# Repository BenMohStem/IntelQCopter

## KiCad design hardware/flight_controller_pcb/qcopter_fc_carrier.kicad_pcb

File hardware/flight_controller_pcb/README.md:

# Flight-controller carrier PCB — draft 0

This first editable PCB is a **logic/sensor carrier** for a Raspberry Pi Pico 2 (RP2350) module. It is not a 40 A power-distribution board. The four ESCs must take battery current directly from a separately rated power-distribution board; this board only routes ESC signal and signal ground. Do not route motor current through this PCB.

## Mechanical assumption

The best match for the described red/white quad is an F450/Q450-style frame. The DJI FlameWheel F450 manual gives a 450 mm diagonal wheelbase, 282 g frame weight, and 9.4 × 5.0 inch propeller dimensions. The latter is a 9.4 inch diameter and 5 inch pitch; it is not a 5 inch racing prop. The board is provisionally 95 × 85 mm with a 30.5 mm square M3 mounting pattern, intended to fit inside the center plates. Verify the specific clone's plate opening and hole coordinates with calipers before ordering a PCB.

## Electrical design

- Host MCU: removable Pico 2 module on two 1×20, 2.54 mm female sockets. External buck module supplies 5.0 V to Pico 2 VSYS from the 3S pack. Never connect the LiPo directly to VSYS.
- Sensors: three 1×4 I²C headers for MPU6050, BMP280, and HMC5883L breakouts; bus is GP4 SDA / GP5 SCL. Breakouts must use 3.3 V logic. Keep sensor leads short, twisted with ground where practical, and away from ESC phase/battery wires.
- Radio: shared SPI0 (GP16 MISO, GP17 LoRa NSS, GP18 SCK, GP19 MOSI), plus individual CS / reset / DIO or GDO lines for one LoRa module and two CC1101 breakouts. All radio interfaces are 3.3 V only; verify exact module pinouts before connecting.
- ESC: four two-pin signal/ground headers in provisional FL, FR, RR, RL order on GP2, GP3, GP6, GP7. The PCB does not carry ESC BEC +5 V pins.
- Battery voltage: the existing 100 kΩ / 27 kΩ divider scales total 3S pack voltage to ADC0/GP26; nominal 12.6 V produces about 2.68 V. It does **not** measure individual cells or state of charge directly. Verify the divider, ADC reference, resistor tolerances, and open-wire behavior before connecting a pack.
- Battery current: GP27/ADC1 receives a filtered 0–3.3 V analog output from an **external current sensor installed in the separately rated PDB**. The flight-controller board carries only the low-voltage sensor signal; battery/ESC current must never flow through it. Select and calibrate the Hall sensor against measured peak current. Do not connect a 5 V sensor output directly to the Pico.
- Cell safety interface: GP28 is `BMS_ALERT`; J17 carries 3.3 V, ground, shared I²C, and alert from an external 3S cell-monitor/protection module connected to the pack's balance lead. The module and its cell-tap wiring are not selected or included. This carrier contains no battery disconnect MOSFETs, fuse, balancing circuit, or independent over/undervoltage protection.
- UART: one 1×4, 3.3 V-only auxiliary UART on GP8/GP9. The user reports a TOFSense-F2 Mini on the F450, but this Pico carrier's wiring and interface have not been validated. Confirm the module mode, line sequence, supply and signal levels before use; add level shifting if required. See the [reported mounting geometry and altitude-fusion requirements](../../docs/lidar-geometry-and-altitude-fusion-2026-11-06.md).
- Four mounting holes are non-plated M3 clearances. The ground plane, decoupling, connector keepouts, mounting plate, and return-current paths still need a reviewed routed layout.

## Current files and validation

`generate_pcb.py` uses the installed KiCad 10.0.6 footprint libraries to generate `qcopter_fc_carrier.kicad_pcb` with footprints, nets, board outline, and mounting holes. The current-sense and cell-monitor connections are interface placeholders. The regenerated draft passes the KiCad geometry DRC (0 geometry violations) but has 76 unconnected pads because no copper has been routed. This is **not ready for fabrication**. There is no completed schematic, routed copper, electrical ERC sign-off, or assembly drawing yet. The pin map and preliminary BOM are adjacent CSV files. The saved DRC report is not a full connectivity/routability sign-off.

The battery software in `firmware/flight_controller/flight_controller.c` filters total-pack voltage with a scalar Kalman filter and estimates SOC by coulomb counting with covariance. Optional SOC correction requires a pack-specific rested-OCV lookup; loaded voltage is not an SOC measurement. The requested policy now warns at 35% estimated SOC and latches disarm at 20%, even airborne, without automatic landing. This inhibits mathematical demands; physical arming/ESC drivers remain disabled and hardware power cutoff is absent. USB status and simulation ROS flags are available; real ADC/current acquisition and handheld LoRa notification remain unfinished. A voltage divider alone does not measure current. Optional cell/BMS inputs require external hardware; without those the software cannot identify a weak individual cell. See [measurement procedures](../../measurements/README.md) and [current integration guide](../../docs/current-model-and-fc-integration.md).

Before manufacturing, confirm the exact F450/Q450 clone, mounting pattern, all breakout-module models, ESC input protocol, switch/arming design, power supply, Pico module orientation, battery connector, external current-sensor output range and peak rating, cell-monitor/BMS module, and TOFSense-F2 Mini electrical interface and measured mount vector. Then create the authoritative schematic, route the board, run DRC/ERC, review 3D clearances, and bench-test rails/current draw with no propellers.

The flight code may provide **software monitoring and low-battery flight modes**, but those do not replace pack-level protection. A software decision depends on the MCU, sensor, firmware, and power remaining operational; it cannot open the battery circuit unless a separately engineered, current-rated hardware protector exists. Do not hard-cut motor power in flight on a low-voltage warning; the intended policy is warn/request a controlled landing and only disarm after landing. Thresholds remain unset pending the exact cell datasheet and load measurements.

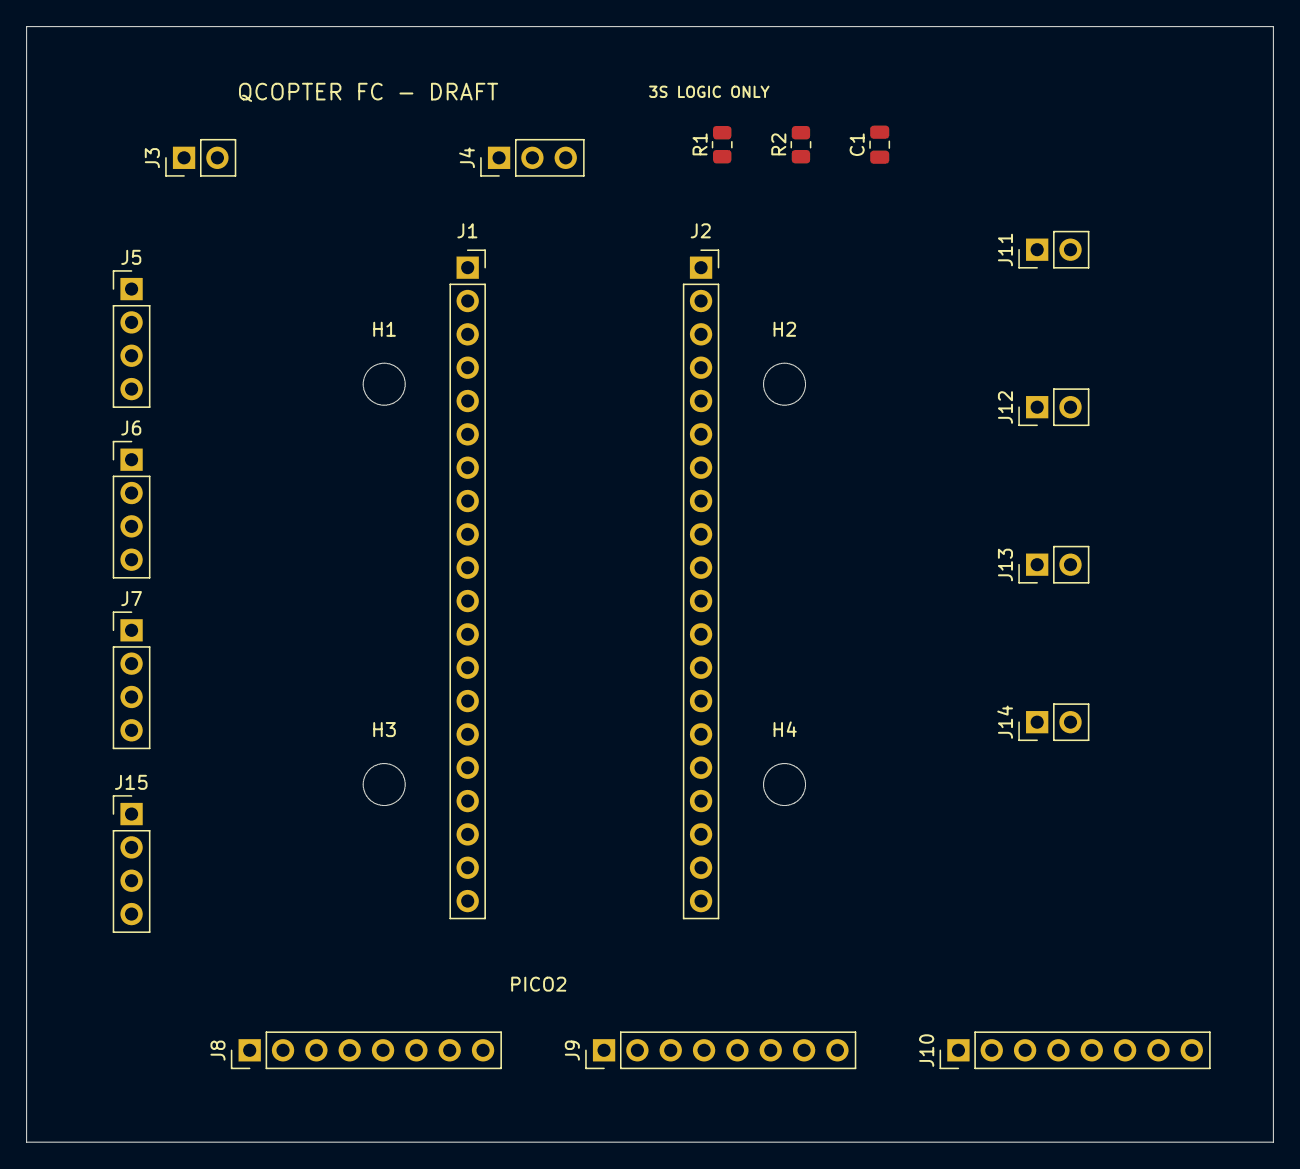
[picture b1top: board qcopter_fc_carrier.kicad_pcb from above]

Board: 4 copper layers, 95.0 x 85.0 mm, 22 parts (0 on the bottom side), 25 nets, no tracks yet.

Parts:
C1: 100n ADC filter; C_0805_2012Metric
H1, H2, H3, H4: M3 mounting hole (NPTH); MountingHole_3.2mm_M3
J1: Pico 2 pins 1-20; PinSocket_1x20_P2.54mm_Vertical
J2: Pico 2 pins 40-21; PinSocket_1x20_P2.54mm_Vertical
J3: 3S input (low-current branch); PinHeader_1x02_P2.54mm_Vertical
J4: External 5 V buck module: VIN/GND/OUT; PinHeader_1x03_P2.54mm_Vertical
J5: MPU6050 I2C; PinHeader_1x04_P2.54mm_Vertical
J6: BMP280 I2C; PinHeader_1x04_P2.54mm_Vertical
J7: HMC5883L I2C; PinHeader_1x04_P2.54mm_Vertical
J8: LoRa SPI/DIO (3V3); PinHeader_1x08_P2.54mm_Vertical
J9: CC1101 A SPI/GDO (3V3); PinHeader_1x08_P2.54mm_Vertical
J10: CC1101 B SPI/GDO (3V3); PinHeader_1x08_P2.54mm_Vertical
J11: ESC FL signal/GND; PinHeader_1x02_P2.54mm_Vertical
J12: ESC FR signal/GND; PinHeader_1x02_P2.54mm_Vertical
J13: ESC RR signal/GND; PinHeader_1x02_P2.54mm_Vertical
J14: ESC RL signal/GND; PinHeader_1x02_P2.54mm_Vertical
J15: AUX UART 3V3/GND/TX/RX; PinHeader_1x04_P2.54mm_Vertical
R1: 100k battery divider; R_0805_2012Metric
R2: 27k battery divider; R_0805_2012Metric

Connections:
+3V3: J2.5, J5.1, J6.1, J7.1, J8.1, J9.1, J10.1, J15.1
+5V_SYS: J2.2, J4.3
AUX_UART_RX: J1.12, J15.4
AUX_UART_TX: J1.11, J15.3
CC1101_A_CS: J2.15, J9.6
CC1101_A_GDO0: J1.16, J9.7
CC1101_A_GDO2: J1.17, J9.8
CC1101_B_CS: J2.14, J10.6
CC1101_B_GDO0: J1.19, J10.7
CC1101_B_GDO2: J1.20, J10.8
ESC_FL_SIG: J1.4, J11.1
ESC_FR_SIG: J1.5, J12.1
ESC_RL_SIG: J1.10, J14.1
ESC_RR_SIG: J1.9, J13.1
GND: C1.2, J1.3, J1.8, J1.13, J1.18, J2.3, J2.7, J2.13, J2.18, J3.2, J4.2, J5.2, J6.2, J7.2, J8.2, J9.2, J10.2, J11.2, J12.2, J13.2, J14.2, J15.2, R2.2
I2C0_SCL: J1.7, J5.4, J6.4, J7.4
I2C0_SDA: J1.6, J5.3, J6.3, J7.3
LORA_DIO0: J1.14, J8.8
LORA_NSS: J2.19, J8.6
LORA_RESET: J1.15, J8.7
SPI0_MISO: J2.20, J8.5, J9.5, J10.5
SPI0_MOSI: J2.16, J8.4, J9.4, J10.4
SPI0_SCK: J2.17, J8.3, J9.3, J10.3
VBAT_3S: J3.1, J4.1, R1.1
VBAT_ADC: C1.1, J2.10, R1.2, R2.1

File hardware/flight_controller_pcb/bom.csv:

Reference,Qty,Item,Footprint / interface,Status
U1,1,Raspberry Pi Pico 2 RP2350 module,40-pin 2.54 mm module,selected module class
J1 J2,2,1x20 female socket for Pico 2,PinSocket_1x20_P2.54mm_Vertical,layout footprint
J3,1,3S LiPo low-current sense/power input,2-pin 2.54 mm header,connector type TBD; ESC current bypasses PCB
J4,1,External buck interface VIN/GND/5V OUT,3-pin 2.54 mm header,buck module and exact pin order TBD
R1,1,100 kOhm battery divider top,0805,provisional
R2,1,27 kOhm battery divider bottom,0805,provisional
C1,1,100 nF ADC filter,0805,provisional
J5-J7,3,I2C sensor breakouts 3V3/GND/SDA/SCL,1x4 2.54 mm header,MPU6050 BMP280 HMC5883L models TBD
J8,1,LoRa SPI and DIO breakout,1x8 2.54 mm header,exact module TBD
J9-J10,2,CC1101 SPI GDO breakout,1x8 2.54 mm header,exact modules TBD
J11-J14,4,ESC signal and signal ground,1x2 2.54 mm header,ESC protocol and plug polarity TBD
J15,1,Auxiliary UART 3V3/GND/TX/RX,1x4 2.54 mm header,exact lidar/interface TBD
H1-H4,4,M3 non-plated mounting holes,3.2 mm drill,30.5 mm pattern provisional

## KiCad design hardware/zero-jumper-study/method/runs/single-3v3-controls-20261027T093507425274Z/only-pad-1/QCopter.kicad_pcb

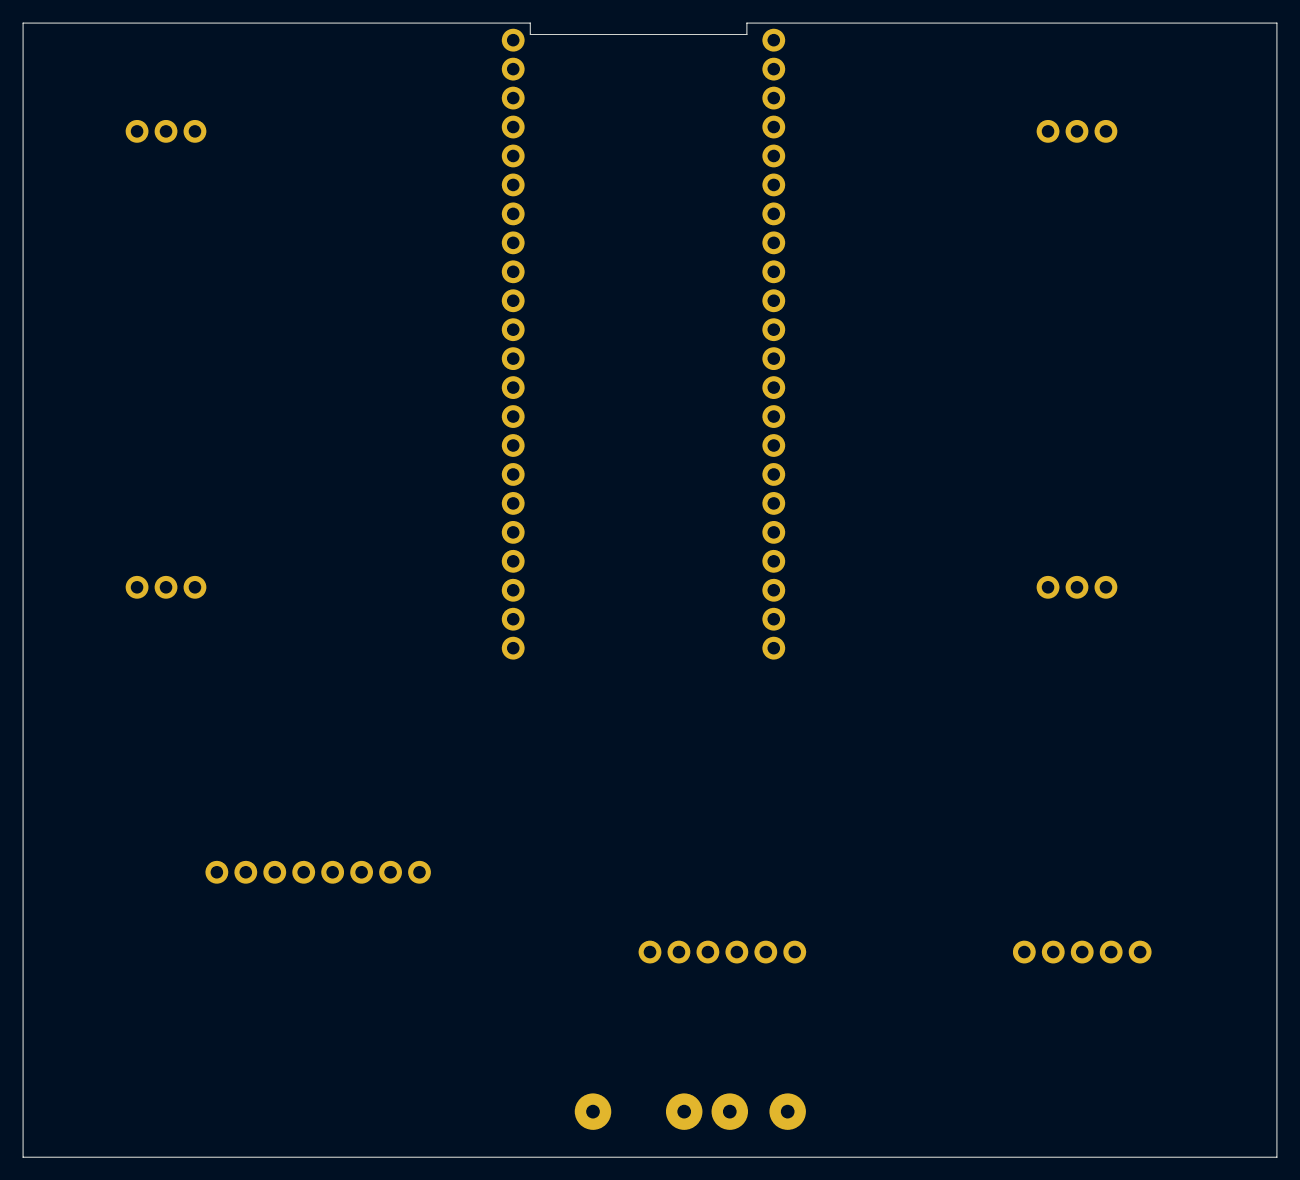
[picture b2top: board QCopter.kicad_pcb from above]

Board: 2 copper layers, 110.0 x 99.5 mm, 9 parts (0 on the bottom side), 15 nets, no tracks yet.

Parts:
J1: LIDAR_SOLDER_WIRES; Lidar_Free_Solder_Lands
J2, J3, J4, J5: ESC_Servo_1x03
U1: ESP32_S3_DevKitC_1_44pin
U2: MPU6050_GY521_1x08
U3: BMP280_GY_1x06
U4: Magnetometer_GY271_1x05

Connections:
3V3: U1.1, U2.1, U3.1, U3.5, U3.6, U4.1
ESC1_SIGNAL: J5.3, U1.4
ESC2_SIGNAL: J2.3, U1.40
ESC3_SIGNAL: J4.3, U1.11
ESC4_SIGNAL: J3.3, U1.27
FC_5V: J1.1, J4.2, U1.21
FC_TX_TO_LIDAR: J1.4, U1.9
GND: J1.2, J2.1, J3.1, J4.1, J5.1, U1.22, U1.23, U1.24, U1.44, U2.2, U2.7, U3.2, U4.2
LIDAR_TO_FC_RX: J1.3, U1.8
MAG_DRDY: U1.38, U4.5
MPU_INT: U1.20, U2.8
MPU_SCL: U1.18, U2.3
MPU_SDA: U1.19, U2.4
SLOW_SCL: U1.37, U3.3, U4.3
SLOW_SDA: U1.36, U3.4, U4.4
